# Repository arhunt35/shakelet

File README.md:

# shakelet
Code and documentation for Shakelet project

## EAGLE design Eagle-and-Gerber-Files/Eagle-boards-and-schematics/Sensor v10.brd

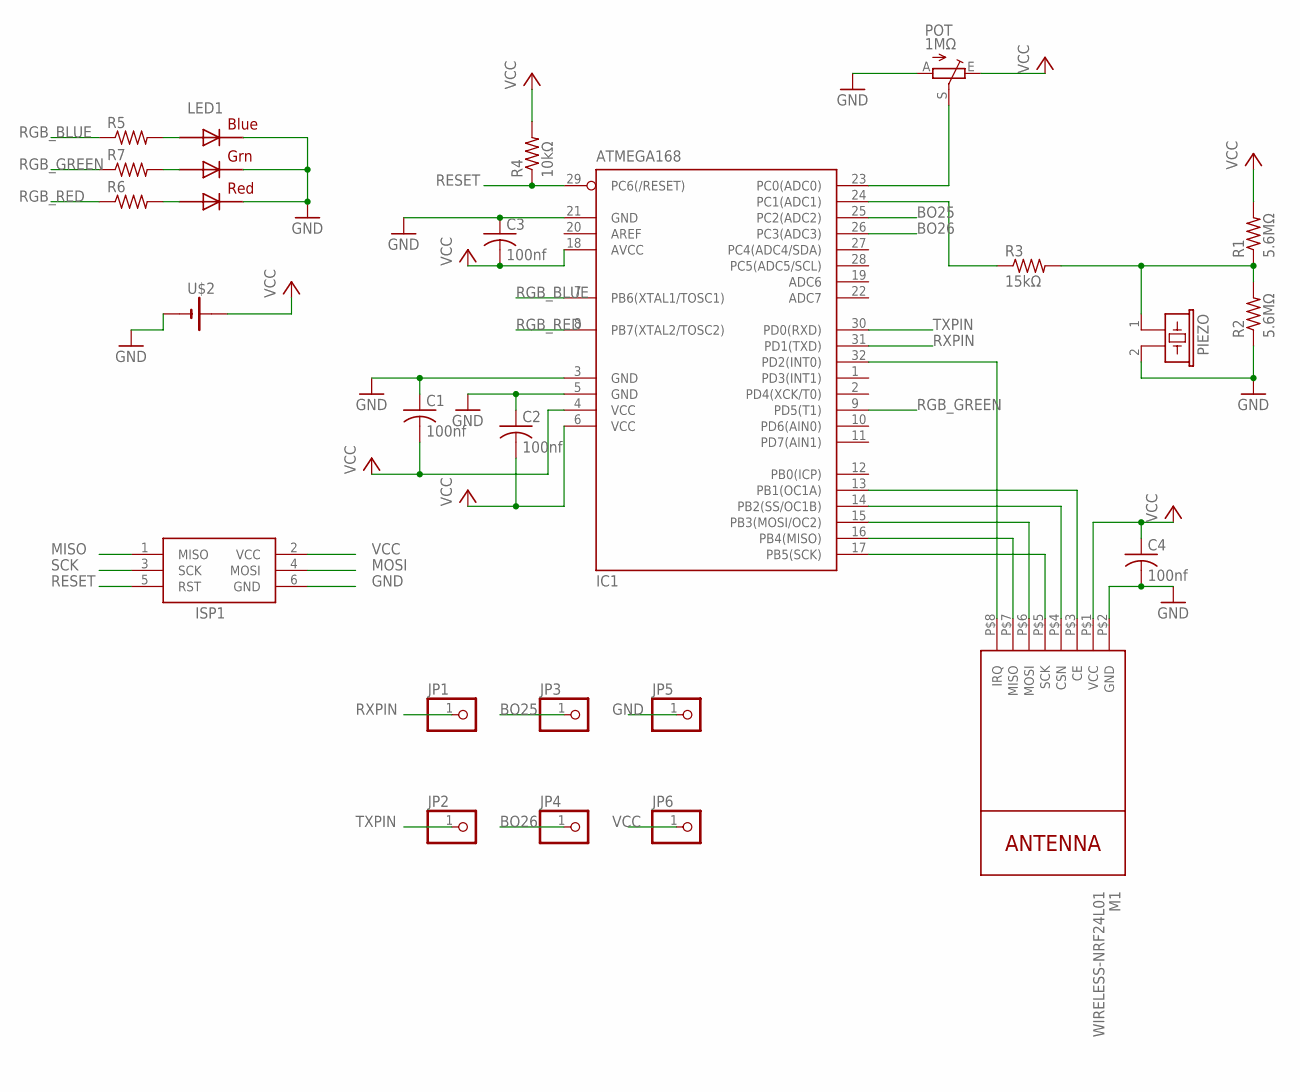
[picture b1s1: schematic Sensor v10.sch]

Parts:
C1, C2, C3, C4: 100nf; C0805
IC1: ATMEGA168; TQFP32-08
ISP1: AVRISP-6; AVRISP
JP1, JP2, JP3, JP4, JP5, JP6: PINHD-1X1; 1X01
LED1: RGBLED5050
M1: WIRELESS-NRF24L01
PIEZO: EFBAA40D101
POT: 1MΩ; CA6V
R1, R2: 5.6MΩ; R0805
R3: 15kΩ; R0805
R4: 10kΩ; R0805
R5, R6, R7: R-US_R0805; R0805
U$2: CR2032SMT; CR2032-SMD

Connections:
BO25: IC1.25 (PC2(ADC2)), JP3.1
BO26: IC1.26 (PC3(ADC3)), JP4.1
GND: C1.1, C2.1, C3.1, C4.2, IC1.3 (GND), IC1.5 (GND), IC1.21 (GND), ISP1.6 (GND), JP5.1, LED1.4 (BLUE_C), LED1.5 (RED_C), LED1.6 (GREEN_C), M1.P$2 (GND), PIEZO.2, POT.A, R2.1, U$2.-$1 (-)
MISO: IC1.16 (PB4(MISO)), ISP1.1 (MISO), M1.P$7 (MISO)
MOSI: IC1.15 (PB3(MOSI/OC2)), ISP1.4 (MOSI), M1.P$6 (MOSI)
unnamed: IC1.13 (PB1(OC1A)), M1.P$3 (CE)
unnamed: IC1.14 (PB2(SS/OC1B)), M1.P$4 (CSN)
unnamed: LED1.3 (BLUE_A), R5.2
unnamed: LED1.1 (GREEN_A), R7.2
unnamed: LED1.2 (RED_A), R6.2
unnamed: IC1.32 (PD2(INT0)), M1.P$8 (IRQ)
unnamed: IC1.23 (PC0(ADC0)), POT.S
unnamed: PIEZO.1, R1.1, R2.2, R3.2
unnamed: IC1.24 (PC1(ADC1)), R3.1
RESET: IC1.29 (PC6(/RESET)), ISP1.5 (RST), R4.1
RGB_BLUE: IC1.7 (PB6(XTAL1/TOSC1)), R5.1
RGB_GREEN: IC1.9 (PD5(T1)), R7.1
RGB_RED: IC1.8 (PB7(XTAL2/TOSC2)), R6.1
RXPIN: IC1.31 (PD1(TXD)), JP1.1
SCK: IC1.17 (PB5(SCK)), ISP1.3 (SCK), M1.P$5 (SCK)
TXPIN: IC1.30 (PD0(RXD)), JP2.1
VCC: C1.2, C2.2, C3.2, C4.1, IC1.4 (VCC), IC1.6 (VCC), IC1.18 (AVCC), ISP1.2 (VCC), JP6.1, M1.P$1 (VCC), POT.E, R1.2, R4.2, U$2.+$1 (+1)

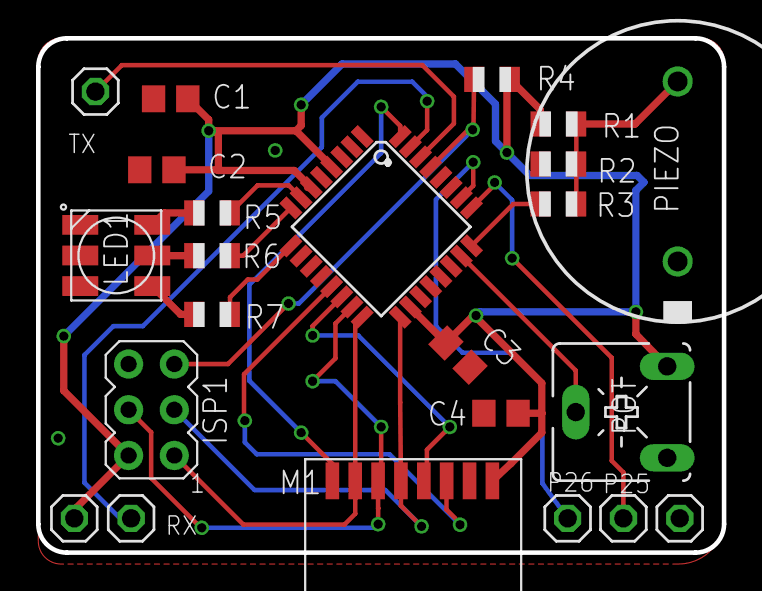
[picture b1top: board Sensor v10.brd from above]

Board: 2 copper layers, 38.1 x 28.6 mm, 24 parts (1 on the bottom side), 22 nets.

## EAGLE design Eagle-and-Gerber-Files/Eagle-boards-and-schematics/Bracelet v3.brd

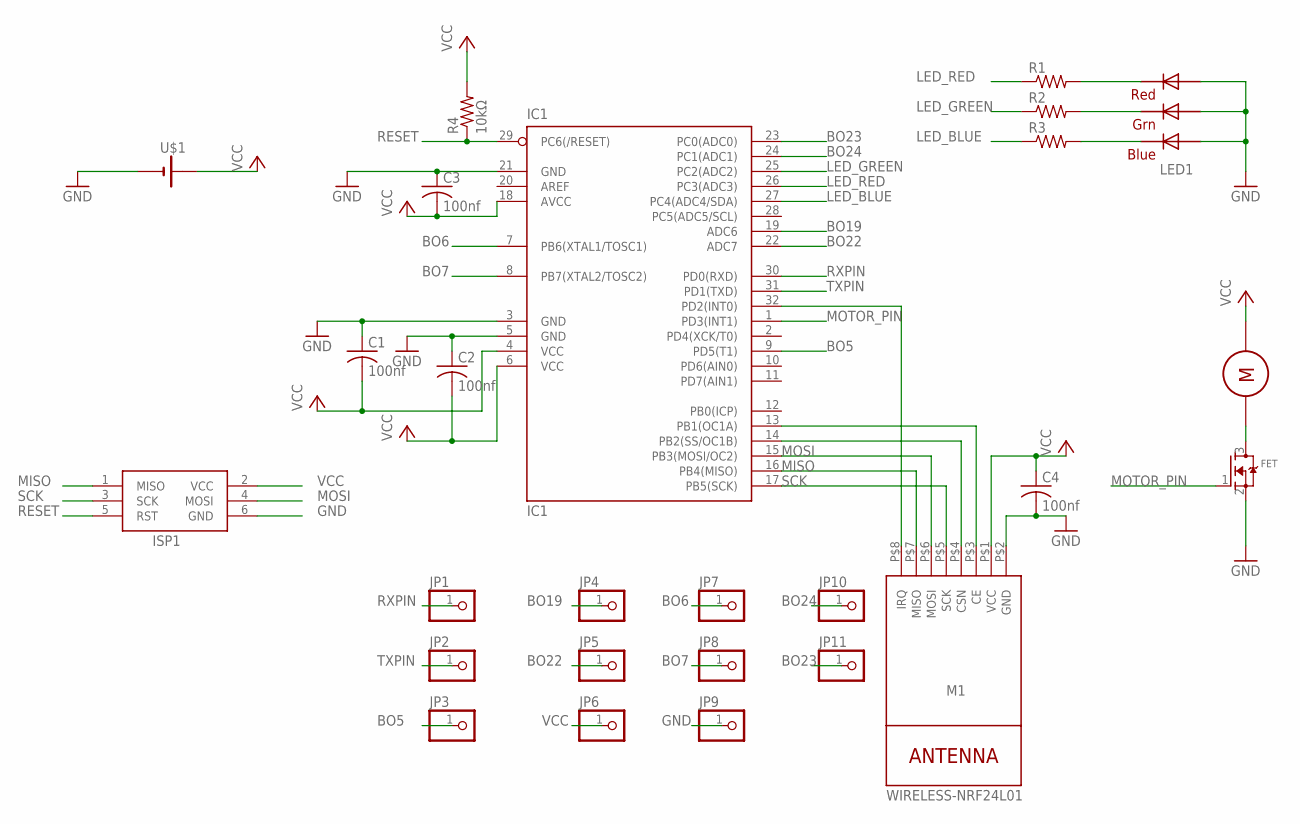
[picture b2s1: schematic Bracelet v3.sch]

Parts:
C1, C2, C3, C4: 100nf; C0805
FET: MOSFET-NREFLOW; SOT23
IC1: IC1; TQFP32-08
ISP1: AVRISP-6; AVRISP
JP1, JP2, JP3, JP4, JP5, JP6, JP7, JP8, JP9, JP10, JP11: PINHD-1X1; 1X01
LED1: RGBLED5050
M1: WIRELESS-NRF24L01
MOTOR: Motor; VIBRATING-MOTOR
R1, R2, R3: R-US_R0805; R0805
R4: 10kΩ; R0805
U$1: CR2032SMT; CR2032-SMD

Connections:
BO5: IC1.9 (PD5(T1)), JP3.1
BO6: IC1.7 (PB6(XTAL1/TOSC1)), JP7.1
BO7: IC1.8 (PB7(XTAL2/TOSC2)), JP8.1
BO19: IC1.19 (ADC6), JP4.1
BO22: IC1.22 (ADC7), JP5.1
BO23: IC1.23 (PC0(ADC0)), JP11.1
BO24: IC1.24 (PC1(ADC1)), JP10.1
GND: C1.1, C2.1, C3.1, C4.2, FET.2 (S), IC1.3 (GND), IC1.5 (GND), IC1.21 (GND), ISP1.6 (GND), JP9.1, LED1.1 (GREEN_A), LED1.2 (RED_A), LED1.3 (BLUE_A), M1.P$2 (GND), U$1.-$1 (-)
LED_BLUE: IC1.27 (PC4(ADC4/SDA)), R3.1
LED_GREEN: IC1.25 (PC2(ADC2)), R2.1
LED_RED: IC1.26 (PC3(ADC3)), R1.1
MISO: IC1.16 (PB4(MISO)), ISP1.1 (MISO), M1.P$7 (MISO)
MOSI: IC1.15 (PB3(MOSI/OC2)), ISP1.4 (MOSI), M1.P$6 (MOSI)
MOTOR_PIN: FET.1 (G), IC1.1 (PD3(INT1))
unnamed: IC1.13 (PB1(OC1A)), M1.P$3 (CE)
unnamed: IC1.14 (PB2(SS/OC1B)), M1.P$4 (CSN)
unnamed: LED1.5 (RED_C), R1.2
unnamed: LED1.6 (GREEN_C), R2.2
unnamed: LED1.4 (BLUE_C), R3.2
unnamed: IC1.32 (PD2(INT0)), M1.P$8 (IRQ)
unnamed: FET.3 (D), MOTOR.P$2
RESET: IC1.29 (PC6(/RESET)), ISP1.5 (RST), R4.1
RXPIN: IC1.30 (PD0(RXD)), JP1.1
SCK: IC1.17 (PB5(SCK)), ISP1.3 (SCK), M1.P$5 (SCK)
TXPIN: IC1.31 (PD1(TXD)), JP2.1
VCC: C1.2, C2.2, C3.2, C4.1, IC1.4 (VCC), IC1.6 (VCC), IC1.18 (AVCC), ISP1.2 (VCC), JP6.1, M1.P$1 (VCC), MOTOR.NAME, R4.2, U$1.+$1 (+1)

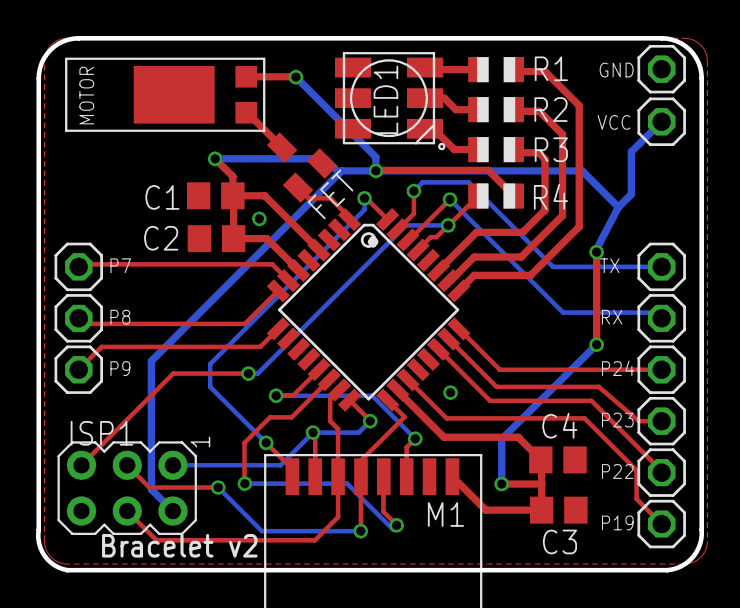
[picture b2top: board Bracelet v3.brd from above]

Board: 2 copper layers, 36.9 x 29.5 mm, 26 parts (1 on the bottom side), 26 nets.

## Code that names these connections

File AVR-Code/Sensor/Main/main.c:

// ------- Preamble -------- //
#include <avr/io.h>                  	// Defines pins, ports, etc
#include <util/delay.h>            		// Functions to waste time
#include <stdlib.h>
#include "pinDefines.h"
#include "ADC.h"
#include "nrf24l01.h"
#include <avr/interrupt.h>
#include <avr/power.h>
#include <avr/sleep.h>
#include "USART.h"

volatile uint8_t sensorID = 2;

volatile uint16_t potValue = 1;
volatile uint16_t piezoValue = 1;
volatile uint16_t baseValue = 1023;

volatile uint16_t lowThresh = 127;
volatile uint16_t highThresh = 127;
volatile uint16_t middleValue = 512;

volatile uint8_t W_buffer[3];

volatile uint32_t combinedADC;
volatile uint16_t lowADC;


void sendSignal(void){
	
	W_buffer[0]=sensorID;
	W_buffer[1]=piezoValue;
	W_buffer[2]=potValue;
	
	transmit_payload(W_buffer);
	reset();
	flashLED();
	//USARTPrint();
	
}

void flashLED(){

	LED_PORT |= (1 << LED_RED)|(1 << LED_GREEN);
	LED_PORT2 |= (1 << LED_BLUE);
	LED_PORT &= ~(1 << LED_RED);
	LED_PORT &= ~(1 << LED_GREEN); 	// Clear all LEDs by setting pin low
	LED_PORT2 &= ~(1 << LED_BLUE); 	// Clear LED by setting pin low

}

void USARTPrint(){
	//USART code for debugging purposes//
	printString("Piezo Value: ");
	printWord(piezoValue);
	printString(" Pot Value: ");
	printWord(potValue);
	printString(" Middle Value: ");
	printWord(middleValue);
	printString("\r\n");
}
	
ISR(ADC_vect){
	//Convert ADCH and ADCL to single integer with range 0 to 1023
	lowADC = ADCL;
	combinedADC = (ADCH<<8)|lowADC;
	
	//Check which ADC conversion just completed and assign ADC value to correct integer
	if(ADMUX & (1<<MUX0)){
		piezoValue = combinedADC;
		middleValue = ((middleValue * 7) + (piezoValue * 3))/10;
	}else{
		potValue = combinedADC*200/baseValue; //Convert to a figure between 0 and 50 to add as padding
		lowThresh = (middleValue - (combinedADC*200)/baseValue);
		highThresh = (middleValue + (combinedADC*200)/baseValue);
	}
	
	//Flip Mux0 to change between ADC0 and ADC1 channel (to swap between piezo and potentiometer
	ADMUX ^= (1<<MUX0);
	
	
	if(piezoValue<lowThresh||piezoValue>highThresh){
		sendSignal();
		_delay_ms(50);		//Don't send signal too often - causes issues with receiver.
	}
	
}


int main(void) 
{
	
	initSPI();
	initNRF24L01();
	//initUSART();
	
	//Init LEDs and flash once to show script running
	LED_DDR|=(1 << LED_RED)|(1 << LED_GREEN);		// set LED pins for output
	LED_DDR2|=(1 << LED_BLUE);		// set blue LED pin for output
	flashLED();  				//Flash to show initiated
	
	initADC();
	ADCSRA |= (1<<ADSC);		// Start conversion - didn't do earlier as not all bits set

	//Reduce power
	power_timer0_disable();
	power_timer1_disable();
	power_timer2_disable();
	power_twi_disable();
		
	//Sleep modes
	set_sleep_mode(SLEEP_MODE_ADC);
	sleep_enable();
	sleep_bod_disable();
	sleep_cpu();
	sleep_mode();
	
	//Power down nrf24
	
	// Mainloop - use asm to stop empty infinite loop being optimised out.
  while(1)
  {
	asm("");
  }

  return 0;
}

	

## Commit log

2016-10-01 Create blank
